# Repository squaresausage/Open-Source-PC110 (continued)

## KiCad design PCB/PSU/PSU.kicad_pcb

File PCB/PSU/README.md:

## Here is the PCB Layout for the PSU board

Layer Stack-up

| Index | Layer name | Description  |
| ----- | ---------- | ------------ |
| 1     | FC         | Top          |
| 2     | IC         | Signal       |
| 3     | IP         | Ground       |
| 4     | BC         | Bottom       |

Here is a render of FC, IC, IP and BC:

Here are 3D models of the PSU board:

PCB statistics report
=====================
- Date: Saturday, March 15, 2025 at 01:16:45 PM
- Project: PSU
- Board name: PSU

Board
-----
- Width: 72.3100 mm
- Height: 44.9600 mm
- Area: 2701.6649 mm²

Pads
----
- Through hole: 20
- SMD: 688
- Connector: 0
- NPTH: 0

Vias
----
- Through vias: 212
- Blind/buried: 0
- Micro vias: 0

Components
----------

|              | Front Side | Back Side | Total |
|--------------|------------|-----------|-------|
|THT:          |          0 |        10 |    10 |
|SMD:          |        171 |        76 |   247 |
|Unspecified:  |          1 |         0 |     1 |
|Total:        |        172 |        86 |   258 |

Drill holes
-----------

| Count | Shape |    X Size |    Y Size | Plated | Via/Pad | Start Layer | Stop Layer |
|-------|-------|-----------|-----------|--------|---------|-------------|------------|
|   203 | Round | 0.3000 mm | 0.3000 mm |    PTH |     Via |          FC |         BC |
|    14 | Round | 0.8000 mm | 0.8000 mm |    PTH |     Pad |          FC |         BC |
|     6 | Round | 1.3000 mm | 1.3000 mm |    PTH |     Pad |          FC |         BC |
|     5 | Round | 0.8000 mm | 0.8000 mm |    PTH |     Via |          FC |         BC |
|     3 | Round | 0.6000 mm | 0.6000 mm |    PTH |     Via |          FC |         BC |
|     1 | Round | 1.0000 mm | 1.0000 mm |    PTH |     Via |          FC |         BC |

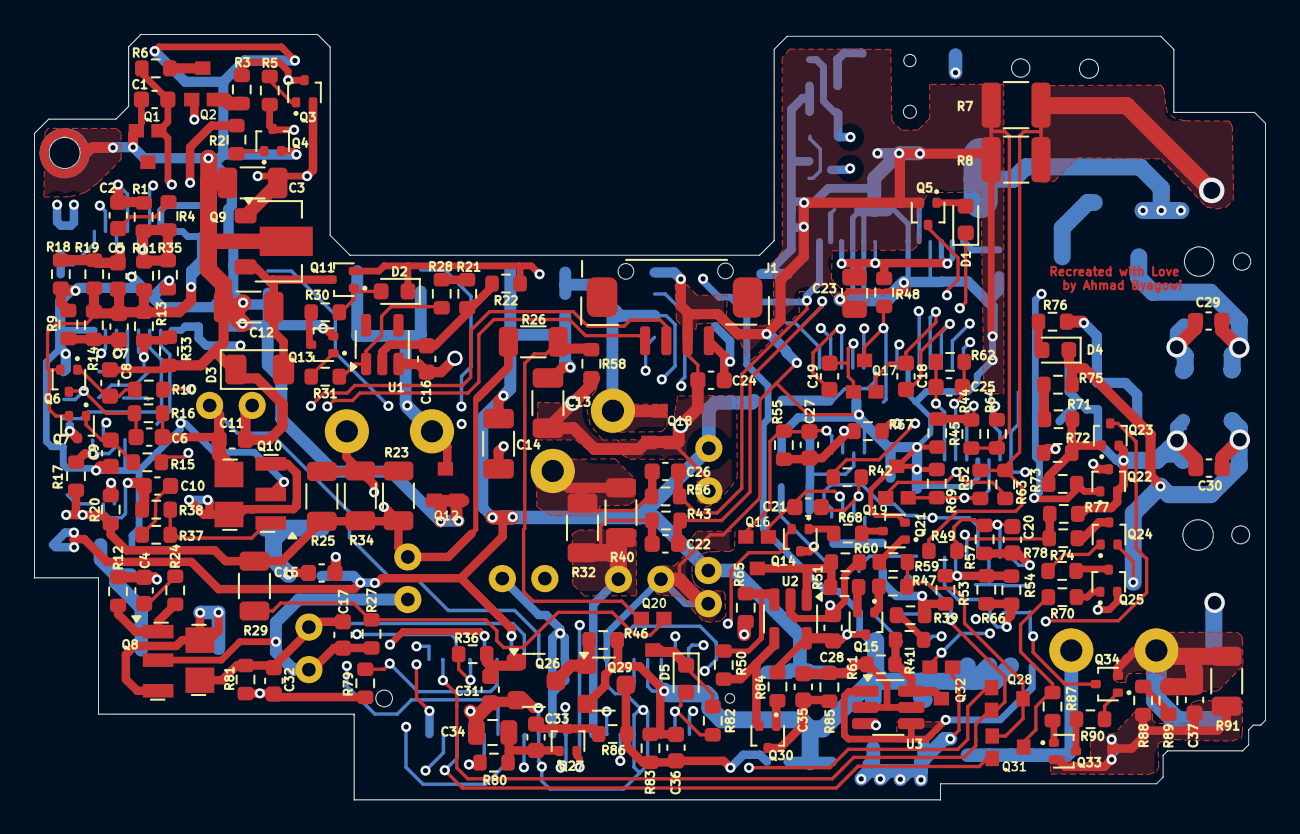
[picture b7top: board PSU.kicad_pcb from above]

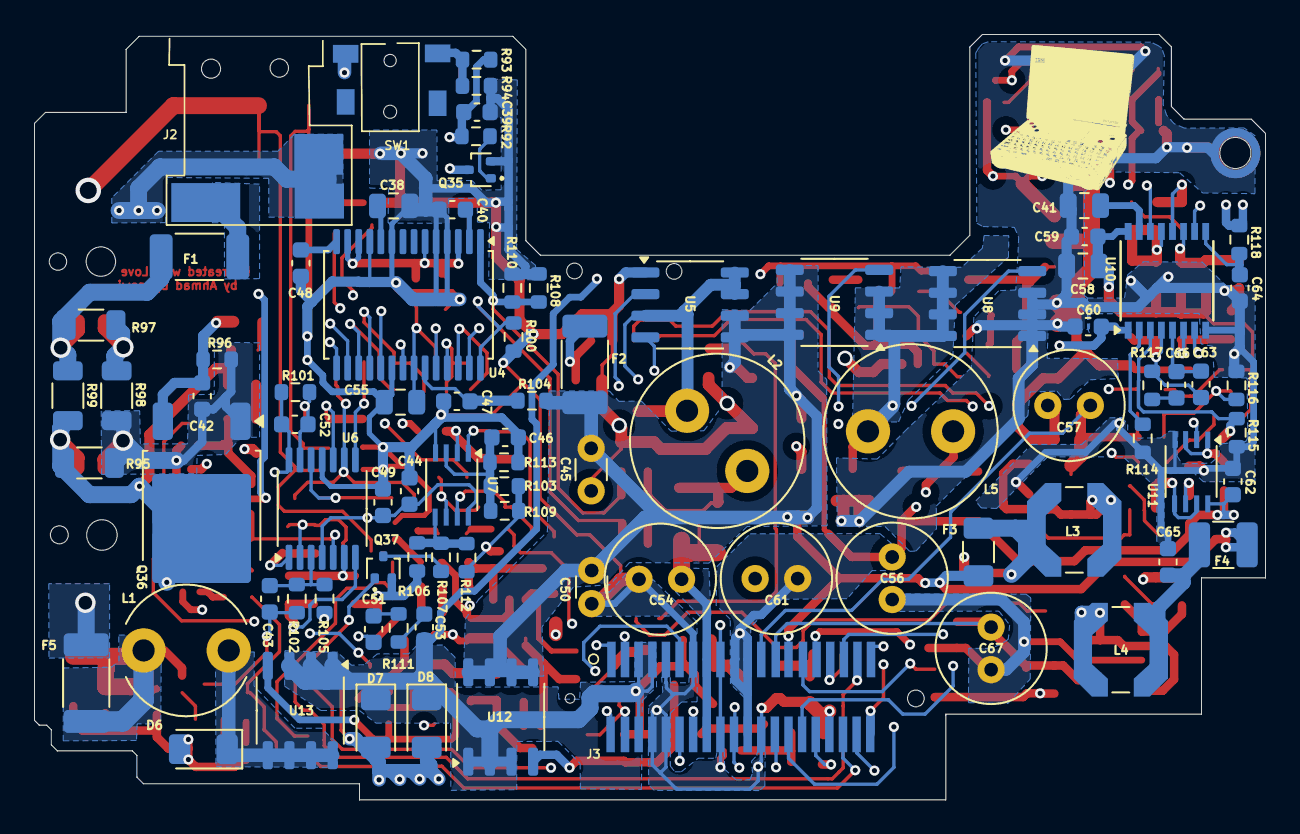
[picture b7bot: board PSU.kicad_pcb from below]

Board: 4 copper layers, 72.3 x 45.0 mm, 258 parts (87 on the bottom side), 155 nets.

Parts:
C1, C5, C7, C16, C24, C28, C36, C46, C47, C59: 150nF; C_0603_1608Metric
C2: 4.7nF; C_0603_1608Metric
C3: 5.2uF; C_1206_3216Metric
C4: 2.5nF; C_0603_1608Metric
C6, C20: 100pF; C_0603_1608Metric
C8, C33: 24nF; C_0603_1608Metric
C9, C17, C22, C26, C29, C30, C32, C39, C40, C48: 10nF; C_0603_1608Metric
C10: 3.6nF; C_0603_1608Metric
C11, C15, C37, C44, C49: 180nF; C_0603_1608Metric
C12: 1.2uF; C_1206_3216Metric
C13, C14: 1.5uF; C_1206_3216Metric
C18, C42, C51, C53, C64: 120nF; C_0603_1608Metric
C19: 18nF; C_0603_1608Metric
C21: 12nF; C_0603_1608Metric
C23, C34, C38, C41, C55, C58: 1.5uF; C_0805_2012Metric
C25, C27, C31, C35, C66: 1.2nF; C_0603_1608Metric
C43: 10pF; C_0603_1608Metric
C45: 33uF 20V; C_Disc_D3.0mm_W1.6mm_P2.50mm
C50: 56uF 25V EC; EC
C52, C60: 1nF; C_0603_1608Metric
C54, C61: 47uF 6.3v; C_Radial_D6.3mm_H11.0mm_P2.50mm
C56: 47uF 6.3V; C_Radial_D6.3mm_H11.0mm_P2.50mm
C57: 15uF 16V; C_Radial_D6.3mm_H11.0mm_P2.50mm
C62, C65: 100nF; C_0603_1608Metric
C63: 5.1nF; C_0603_1608Metric
C67: 18uF 50V; C_Radial_D6.3mm_H11.0mm_P2.50mm
D1: 8-2; D_0603_1608Metric
D2: 5-9; D_0603_1608Metric
D3, D6: DNP; D_1206_3216Metric
D4: 18; D_0603_1608Metric
D5: 3^9; D_0603_1608Metric
D7, D8: s.3 4F; D_1206_3216Metric
F1, F5: 2.5A; Fuse_2010_5025Metric
F2: 830mA; Fuse_2010_5025Metric
F3: 15; Fuse_1206_3216Metric
F4: 10; Fuse_1210_3225Metric
G1: LOGO; logo
J1: Backllight_Connector
J2: PSU_Jack
J3: PSU_Connector_Receptor
L1: 10uH; L_Radial_D7.5mm_P5.00mm_Fastron_07P
L2, L5: 10uH; L_Radial_D10.0mm_P5.00mm_Fastron_07M
L3: 68uH; L_Coilcraft_LPS5030
L4: 470uH; L_Coilcraft_LPS5030
Q1: R4C; 3D
Q2, Q32: K; 3D
Q3, Q6, Q7, Q11, Q14, Q24, Q34: 6LS; SOT-416
Q4, Q13, Q15, Q33, Q37: 8LR; SOT-416
Q5, Q21, Q22, Q23, Q27, Q30, Q35: 8C; SOT-416
Q8: 303 5H; SOT-powerT
Q9: KD 3.E; SOT-89-3
Q10: 103 5G; SOT-powerT
Q12, Q18: Q; 3D
Q16, Q17, Q19: M2P; 3D
Q20, Q28, Q31: W6; 3D
Q25: 8LB; SOT-416
Q26: G16; SOT-23-PC110
Q29: H15; SOT-23-PC110
Q36: 3P4J; TO-252-2
R1, R50, R66, R82, R108: DNP; R_0603_1608Metric
R2, R10, R21, R31, R70, R74, R83, R87, R90: 470k; R_0603_1608Metric
R3, R36, R65, R71, R72, R75, R76, R93: 1k; R_0603_1608Metric
R4, R11, R13, R17, R19, R20, R30, R33, R35, R44, R52, R61, R63, R64, R85, R86, R103, R114, R117: 10k; R_0603_1608Metric
R5, R15, R22, R54, R57, R59, R77, R80, R84, R92, R105: 100k; R_0603_1608Metric
R6, R38: 470; R_0603_1608Metric
R7, R8: 0.1; R_1210_3225Metric
R9, R18, R112, R113: 20k; R_0603_1608Metric
R12: 2.2k; R_0603_1608Metric
R14: 12k; R_0603_1608Metric
R16: 130k; R_0603_1608Metric
R23, R25, R32, R34: 0.1; R_1206_3216Metric
R24: 220; R_0603_1608Metric
R26: 103 (RT1); R_1206_3216Metric
R27, R39, R41, R51, R58, R60, R106: 4.7k; R_0603_1608Metric
R28: 0; R_0603_1608Metric
R29: 103 (RT2); R_1206_3216Metric
R37: 120; R_0603_1608Metric
R40: 0.22; R_1206_3216Metric
R42, R47, R67, R68, R73, R79, R94: 47k; R_0603_1608Metric
R43, R56: 300; R_0603_1608Metric
R45, R62, R69, R81, R101, R109: 200k; R_0603_1608Metric
R46, R55, R88, R89: 1M; R_0603_1608Metric
R48, R104, R118: 100; R_0603_1608Metric
R49, R53, R78, R102: 300k; R_0603_1608Metric
R91, R95, R97: DNP; R_1206_3216Metric
R96: 1.8k; R_0603_1608Metric
R98, R99: 0; R_1206_3216Metric
R100, R110: 7.5k; R_0603_1608Metric
R107: 2k; R_0603_1608Metric
R111: 33; R_0603_1608Metric
R115: 11K; R_0603_1608Metric
R116: 15k; R_0603_1608Metric
SW1: PSU-SW1
U1: D9D; SOT-23-5
U2: TA; SOT-23-5
U3: 6.5 5F; SOT-23-6_Handsoldering
U4: MAX786CAI; TSSOP-28_6.1x9.7mm_P0.65mm
U5: K2337; SOP-8_3.9x4.9mm_P1.27mm
U6: 7064; TSSOP-14_4.4x5mm_P0.65mm
U7: 5W01; SSOP-8-PSU
U8, U9: 2556; SOP-8_3.9x4.9mm_P1.27mm
U10: 9742; SSOP-16_4.4x5.2mm_P0.65mm
U11: 7W14; SSOP-8-PSU
U12, U13: J421; SOP-8_3.9x4.9mm_P1.27mm

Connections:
BATT_POS: R7.2, R8.2, R49.1, R52.2, R63.2
C1_1: C2.1, R4.1
C1_2: C2.2, R1.1, U10.12
C6_1: C4.1, R24.2
C6_2: C4.2, R12.2, U11.2
C8_1: C7.1, R9.2, R14.2, U10.6
C14_2: C12.2, D3.2, Q9.3, Q11.3
C31_1: C33.1, Q27.3, R86.2
C32_1: C33.2, C34.1, Q27.1, R80.1
C33_1: C31.1, Q26.1, R36.1
C35_2: C36.2, Q29.3, R83.2, R86.1, U12.4
C36_1: C35.1, R61.1, R85.2, U3.2, U3.5
C36_2: C35.2, Q30.3, R85.1
D1_2: D1.2, Q5.1
D2_3_PC110: J3.26, Q23.3
D18_2_3_PC110: J1.1, J3.40
D28_1_PC110: C6.2, C11.1, C57.1, J3.12, Q10.4, R16.2
F3_1: C15.1, F3.1, L3.1
F65_ENAVEE_PC110: J3.35, R15.1
GND: C1.1, C3.1, C8.2, C9.1, C11.2, C12.1, C13.2, C14.2, C15.2, C16.2, C17.1, C23.1, C24.1, C28.1, C30.1, C31.2, C34.2, C37.1, C38.2, C39.2, C40.1, C41.1, C42.2, C44.2, C45.1, C46.2, C47.1, C48.2, C49.2, C50.1, C51.1, C54.2, C55.1, C56.1, C57.2, C58.1, C59.2, C60.1, C61.2, C62.1, C64.2, C65.2, C67.1, D3.1, D6.2, J1.3, J3.5, J3.7, J3.9, J3.24, J3.25, J3.29, J3.32, J3.37, Q1.1, Q4.2, Q5.2, Q8.2, Q9.2, Q10.2, Q12.1, Q12.3, Q13.2, Q18.1, Q18.3, Q19.2, Q21.2, Q22.2, Q23.2, Q25.2, Q26.2, Q27.2, Q33.2, Q35.2, Q36.1, Q37.2, R7.1, R8.1, R9.1, R18.2, R27.1, R33.2, R35.2, R39.2, R44.1, R45.1, R53.1, R58.1, R60.2, R64.1, R69.2, R72.1, R77.2, R88.1, R91.1, R94.2, R95.2, R96.2, R98.2, R100.2, R105.2, R106.2, R108.1, R110.1, R113.2, R114.2, R115.2, R116.1, U1.3, U2.2, U3.3, U4.4, U4.5, U4.9, U4.11, U4.20, U5.1, U6.11, U7.4, U8.1, U8.2, U8.3, U10.8, U11.4
J1_4: C24.2, F2.1, J1.4
J5_6_PC110: D1.1, J3.6, Q32.1
J5_33_PC110: C39.1, J3.33, R92.1, R93.2
JRC_IN1+: C43.1, R102.1, R105.1, U6.3
JRC_IN1-: C20.2, R49.2, R57.2, U6.2
JRC_IN2+: R77.1, R78.1, U6.5
JRC_IN2-: R53.2, R54.2, R66.2, U6.6
JRC_IN3+: R44.2, R45.2, U6.10
JRC_IN3-: C25.2, Q19.3, R62.2, R63.1, U6.9
JRC_IN4+: Q19.1, R52.1, R69.1, U6.12
JRC_IN4-: C52.2, R64.2, R101.2, U6.13
JRC_VDD: C44.1, C49.1, Q3.3, R3.1, U6.4, U7.8
L1_2: D6.1, L1.2, U13.5, U13.6, U13.7, U13.8
L2_2: L3.2, Q10.3, Q10.5
M38_P20_PC110: J3.19, Q28.1, Q37.1
M38_P21_PC110: J3.39, Q28.3
M38_P52_PC110: J3.18, R2.1
M38_P53_PC110: J3.38, Q31.1
M38_P60_PC110: C25.1, J3.1, R62.1, U6.8
M38_P61_PC110: C52.1, J3.2, R42.1, R101.1, U6.14
M38_P63_PC110: C20.1, J3.21, R57.1, R67.2, U6.1
M38_P64_PC110: J3.27, R54.1, R66.1, U6.7
M38_VREF_PC110: C1.2, J3.30, Q1.3, Q14.2, R6.1
MAX_BST3: C19.2, Q17.3, U4.25
MAX_BST5: C18.2, Q17.1, U4.18
MAX_CS3: C26.2, R56.2, R108.2, R110.2, U4.1
MAX_CS5: L5.1, R23.2, R25.2, R34.2, U4.15
MAX_DH3: U4.27, U5.4
MAX_DH5: U4.16, U9.4
MAX_DL3: U4.24, U5.2
MAX_DL5: U4.19, U8.4
MAX_FB3: C22.2, R43.2, R100.1, U4.28
MAX_LX3: C19.1, L2.1, Q18.2, U4.26, U5.3, U5.7, U5.8
MAX_LX5: C18.1, L5.2, Q12.2, U4.17, U8.5, U8.6, U8.7, U8.8, U9.1, U9.2, U9.3
MAX_REF: C38.1, U4.10
MAX_SS3: C40.2, U4.2
MAX_SS5: C48.1, U4.14
MAX_VL: C55.2, Q17.2, R48.1, U4.22
MAX_VL+: C47.2, R104.1, U4.23
ON3_ON5_VH_SHDN#: C23.2, R48.2, U4.3, U4.6, U4.12, U4.13
PNET1_PC110: C22.1, C54.1, J3.8, J3.28, R32.1, R40.1, R43.1
PNET4_PC110: C36.1, C53.2, D2.1, D7.1, D8.1, J3.3, J3.4, J3.23, Q11.2, Q29.2, R22.2, R46.2, R83.1, U12.1, U12.2, U12.3, U13.1, U13.2, U13.3
PNET5_PC110: C28.2, C56.2, C61.1, C62.2, J3.10, J3.11, J3.31, Q2.3, Q15.3, R17.2, R20.2, R23.1, R25.1, R26.1, R29.2, R34.1, R84.2, R118.1, U2.5, U4.21, U11.8
PWR_IN_10v5: C30.2, D4.1, D7.2, D8.2, Q24.2, Q32.3, Q36.2, R75.2, R95.1, R99.2
PWR_IN_NEG: C29.1, J2.2, J2.3, R97.2, R98.1
PWR_IN_POS: F1.2, J2.1
PWR_IN_POS_Fuse: C29.2, F1.1, R97.1, R99.1
Q3_1: Q4.1, R2.2
Q3_3: Q4.3, Q5.3, Q22.3, R5.2
Q4_1: Q3.1, R5.1
Q6_2: C5.1, C7.2, C58.2, C59.1, Q6.2, Q7.2, R11.2, R13.1, R14.1, R19.2, U10.16
Q7_1: C8.1, Q6.1, R10.1
Q7_3: C6.1, Q6.3, R16.1, R116.2, U10.14
Q8_1: Q8.1, R12.1, R24.1
Q8_5: L4.1, Q8.3, Q8.5
Q9_1: Q10.1, R37.1, R38.1
Q13_3: Q13.3, R30.1
Q14_2: D5.1, Q20.2, R82.1
Q20_1: C27.2, Q16.1, R55.2, U7.1
Q22_1: Q24.1, R74.1
Q27_3: Q26.3, Q29.1, R46.1
Q29_2: Q31.2, R70.1, R87.2
Q30_2: Q28.2, Q31.3, R47.2, R59.2
Q33_2: C37.2, F5.2, L1.1, Q34.2, R89.2, R91.2
Q33_3: C43.2, Q34.3, R102.2
Q36_3: Q37.3, R107.2
Q43_2_PC110: C17.2, C32.2, C67.2, J3.13, Q8.4, R81.2
Q49_1_PC110: D5.2, J3.22, R82.2
R2_2: Q2.1, R3.2
R6_2: Q2.2, R6.2
R11_1: R20.1, U10.7, U11.6
R17_2: C9.2, Q7.1, R15.2
R19_1: R17.1, U10.10, U11.1, U11.3
R20_1: C5.2, R18.1, R19.1, U10.11
R21_1: Q13.1, R31.1
R21_2: R28.1, R31.2, U1.1
R24_2: C10.1, R38.2, U11.5, U11.7
R26_2: R21.2, R28.2
R31_1: C16.1, R21.1, R22.1, U1.2
R32_1: R1.2, R4.2, R11.1, R35.1, U10.13
R35_2: D2.2, Q11.1, R30.2
R36_1: C63.2, R13.2, R33.1, R117.1, U10.4
R36_2: C10.2, R37.2
R38_1: Q20.3, R27.2, R29.1
R48_2: Q20.1, R26.2, R58.2
R50_1: Q30.2, R50.1, U2.4
R50_2: R50.2, R65.2, U2.3
R51_1: Q16.2, R51.1, R60.1, U2.1
R51_2: Q15.2, R51.2
R54_2: R39.1, R41.2
R56_1: C26.1, L2.2, R32.2, R40.2, R56.1
R59_1: Q21.1, R59.1
R61_1: Q15.1, R47.1
R68_1: Q14.1, R68.1
R68_2: Q21.3, R68.2
R70_2: Q25.3, R74.2
R72_1: D4.2, R76.1
R72_2: C42.1, Q36.3, R76.2, R96.1
R73_2: Q25.1, R70.2
R73_2_PC110: J3.15, R79.2
R76_1: R71.1, R75.1
R77_1: Q23.1, R71.2, R72.2, R73.1
R77_2: Q22.1, Q35.3, R73.2
R78_2: Q24.3, R78.2
R80_1: C32.1, Q7.3, R79.1, R81.1, R115.1, U10.3
R82_1: Q30.1, R84.1
R88_1: Q33.1, R87.1
R89_1: R88.2, R89.1
R91_1: Q33.3, R90.1
R91_2: Q34.1, R90.2
R92_2: Q35.1, R92.2
R104_1: R106.1, R107.1, R112.1, U7.5
R106_1: C51.2, R111.1
R106_2: C53.1, R111.2
R111_2: Q14.3, R103.2, R109.2, R112.2
R111_!: C46.1, R103.1, R109.1, R113.1, U7.3
R115_2: C66.2, R117.2
R284_2_PC110: C13.1, C14.1, C45.2, C50.2, F2.2, F3.2, F4.2, J3.14, R104.2, U5.5, U5.6, U9.5, U9.6, U9.7, U9.8, U12.5, U12.6, U12.7, U12.8
R284_2_PC110_Fuse: C65.1, F4.1, L4.2
R412_1_PC110: J1.2, J3.20
SW1_2: R93.1, R94.1, SW1.2
U3_1: U3.1, U3.4, U13.4
U3_6: Q32.2, R41.1, R61.2, U3.6
U6_2: C27.1, R55.1, R67.1, U7.2
U6_6: C21.1, R42.2, U7.6
U6_7: C21.2, Q16.3, U7.7
U11_1: C60.2, R65.1, U10.1
U11_2: R114.1, U10.2
U11_5: C63.1, C66.1, U10.5
U11_9: C64.1, R118.2, U10.9
U11_15: C41.2, U10.15
U21_131_PC110: J3.34, R10.2
U54_1D_PC110: J3.17, R36.2
U54_1Q_PC110: J3.36, R80.2
U54_VCC_PC110: C3.2, J3.16, Q3.2, Q9.1, SW1.1

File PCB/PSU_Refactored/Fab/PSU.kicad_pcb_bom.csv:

Designator,Quantity,Value,Footprint,Package,MPN,DNP,Mount_Type
"C1, C16, C24, C28, C36, C46, C47, C5, C59, C7",10,150nF,C_0603_1608Metric,,,,smt
C10,1,3.6nF,C_0603_1608Metric,,,,smt
"C11, C15, C37, C44, C49",5,180nF,C_0603_1608Metric,,,,smt
C12,1,1.2uF,C_1206_3216Metric,,,,smt
"C13, C14",2,1.5uF,C_1206_3216Metric,,,,smt
"C17, C22, C26, C29, C30, C32, C39, C40, C48, C9",10,10nF,C_0603_1608Metric,,,,smt
"C18, C42, C51, C53, C64",5,120nF,C_0603_1608Metric,,,,smt
C19,1,18nF,C_0603_1608Metric,,,,smt
C2,1,4.7nF,C_0603_1608Metric,,,,smt
"C20, C6",2,100pF,C_0603_1608Metric,,,,smt
C21,1,12nF,C_0603_1608Metric,,,,smt
"C23, C34, C38, C41, C55, C58",6,1.5uF,C_0805_2012Metric,,,,smt
"C25, C27, C31, C35, C66",5,1.2nF,C_0603_1608Metric,,,,smt
C3,1,5.2uF,C_1206_3216Metric,,,,smt
"C33, C8",2,24nF,C_0603_1608Metric,,,,smt
C4,1,2.5nF,C_0603_1608Metric,,,,smt
C43,1,10pF,C_0603_1608Metric,,,,smt
C45,1,33uF 20V,C_Disc_D3.0mm_W1.6mm_P2.50mm,,,,tht
C50,1,56uF 25V EC,EC,,,,tht
"C52, C60",2,1nF,C_0603_1608Metric,,,,smt
"C54, C61",2,47uF 6.3v,C_Radial_D6.3mm_H11.0mm_P2.50mm,,,,tht
C56,1,47uF 6.3V,C_Radial_D6.3mm_H11.0mm_P2.50mm,,,,tht
C57,1,15uF 16V,C_Radial_D6.3mm_H11.0mm_P2.50mm,,,,tht
"C62, C65",2,100nF,C_0603_1608Metric,,,,smt
C63,1,5.1nF,C_0603_1608Metric,,,,smt
C67,1,18uF 50V,C_Radial_D6.3mm_H11.0mm_P2.50mm,,,,tht
D1,1,8-2,D_0603_1608Metric,,,,smt
D2,1,5-9,D_0603_1608Metric,,,,smt
D3,1,DNP,D_1206_3216Metric,,,Yes,smt
D4,1,18,D_0603_1608Metric,,,,smt
D5,1,3^9,D_0603_1608Metric,,,,smt
D6,1,DNP,D_1206_3216Metric,,,Yes,smt
"D7, D8",2,s.3 4F,D_1206_3216Metric,,,,smt
"F1, F5",2,2.5A,Fuse_2010_5025Metric,,,,smt
F2,1,830mA,Fuse_2010_5025Metric,,,,smt
F3,1,15,Fuse_1206_3216Metric,,,,smt
F4,1,10,Fuse_1210_3225Metric,,,,smt
J1,1,Backllight_Connector,Backllight_Connector,,,,smt
J2,1,PSU_Jack,PSU_Jack,,,,smt
J3,1,PSU_Connector_Receptor,PSU_Connector_Receptor,,,,smt
L1,1,10uH,L_Radial_D7.5mm_P5.00mm_Fastron_07P,,,,tht
"L2, L5",2,10uH,L_Radial_D10.0mm_P5.00mm_Fastron_07M,,,,tht
L3,1,68uH,L_Coilcraft_LPS5030,,,,smt
L4,1,470uH,L_Coilcraft_LPS5030,,,,smt
Q1,1,R4C,3D,,,,smt
Q10,1,103 5G,SOT-powerT,,,,smt
"Q11, Q14, Q24, Q3, Q34, Q6, Q7",7,6LS,SOT-416,,,,smt
"Q12, Q18",2,Q,3D,,,,smt
"Q13, Q15, Q33, Q37, Q4",5,8LR,SOT-416,,,,smt
"Q16, Q17, Q19",3,M2P,3D,,,,smt
"Q2, Q32",2,K,3D,,,,smt
"Q20, Q28, Q31",3,W6,3D,,,,smt
"Q21, Q22, Q23, Q27, Q30, Q35, Q5",7,8C,SOT-416,,,,smt
Q25,1,8LB,SOT-416,,,,smt
Q26,1,G16,SOT-23-PC110,,,,smt
Q29,1,H15,SOT-23-PC110,,,,smt
Q36,1,3P4J,TO-252-2,,,,smt
Q8,1,303 5H,SOT-powerT,,,,smt
Q9,1,KD 3.E,SOT-89-3,,,,smt
R1,1,DNP,R_0603_1608Metric,,,Yes,smt
"R10, R2, R21, R31, R70, R74, R83, R87, R90",9,470k,R_0603_1608Metric,,,,smt
"R100, R110",2,7.5k,R_0603_1608Metric,,,,smt
"R101, R109, R45, R62, R69, R81",6,200k,R_0603_1608Metric,,,,smt
"R102, R49, R53, R78",4,300k,R_0603_1608Metric,,,,smt
"R103, R11, R114, R117, R13, R17, R19, R20, R30, R33, R35, R4, R44, R52, R61, R63, R64, R85, R86",19,10k,R_0603_1608Metric,,,,smt
"R104, R118, R48",3,100,R_0603_1608Metric,,,,smt
"R105, R15, R22, R5, R54, R57, R59, R77, R80, R84, R92",11,100k,R_0603_1608Metric,,,,smt
"R106, R27, R39, R41, R51, R58, R60",7,4.7k,R_0603_1608Metric,,,,smt
R107,1,2k,R_0603_1608Metric,,,,smt
R108,1,DNP,R_0603_1608Metric,,,Yes,smt
R111,1,33,R_0603_1608Metric,,,,smt
"R112, R113, R18, R9",4,20k,R_0603_1608Metric,,,,smt
R115,1,11K,R_0603_1608Metric,,,,smt
R116,1,15k,R_0603_1608Metric,,,,smt
R12,1,2.2k,R_0603_1608Metric,,,,smt
R14,1,12k,R_0603_1608Metric,,,,smt
R16,1,130k,R_0603_1608Metric,,,,smt
"R23, R25, R32, R34",4,0.1,R_1206_3216Metric,,,,smt
R24,1,220,R_0603_1608Metric,,,,smt
R26,1,103 (RT1),R_1206_3216Metric,,,,smt
R28,1,0,R_0603_1608Metric,,,,smt
R29,1,103 (RT2),R_1206_3216Metric,,,,smt
"R3, R36, R65, R71, R72, R75, R76, R93",8,1k,R_0603_1608Metric,,,,smt
R37,1,120,R_0603_1608Metric,,,,smt
"R38, R6",2,470,R_0603_1608Metric,,,,smt
R40,1,0.22,R_1206_3216Metric,,,,smt
"R42, R47, R67, R68, R73, R79, R94",7,47k,R_0603_1608Metric,,,,smt
"R43, R56",2,300,R_0603_1608Metric,,,,smt
"R46, R55, R88, R89",4,1M,R_0603_1608Metric,,,,smt
R50,1,DNP,R_0603_1608Metric,,,Yes,smt
R66,1,DNP,R_0603_1608Metric,,,Yes,smt
"R7, R8",2,0.1,R_1210_3225Metric,,,,smt
R82,1,DNP,R_0603_1608Metric,,,Yes,smt
R91,1,DNP,R_1206_3216Metric,,,Yes,smt
R95,1,DNP,R_1206_3216Metric,,,Yes,smt
R96,1,1.8k,R_0603_1608Metric,,,,smt
R97,1,DNP,R_1206_3216Metric,,,Yes,smt
"R98, R99",2,0,R_1206_3216Metric,,,,smt
SW1,1,PSU-SW1,PSU-SW1,,,,smt
U1,1,D9D,SOT-23-5,,,,smt
U10,1,9742,SSOP-16_4.4x5.2mm_P0.65mm,,,,smt
U11,1,7W14,SSOP-8-PSU,,,,smt
"U12, U13",2,J421,SOP-8_3.9x4.9mm_P1.27mm,,,,smt
U2,1,TA,SOT-23-5,,,,smt
U3,1,6.5 5F,SOT-23-6_Handsoldering,,,,smt
U4,1,MAX786CAI,TSSOP-28_6.1x9.7mm_P0.65mm,,,,smt
U5,1,K2337,SOP-8_3.9x4.9mm_P1.27mm,,,,smt
U6,1,7064,TSSOP-14_4.4x5mm_P0.65mm,,,,smt
U7,1,5W01,SSOP-8-PSU,,,,smt
"U8, U9",2,2556,SOP-8_3.9x4.9mm_P1.27mm,,,,smt

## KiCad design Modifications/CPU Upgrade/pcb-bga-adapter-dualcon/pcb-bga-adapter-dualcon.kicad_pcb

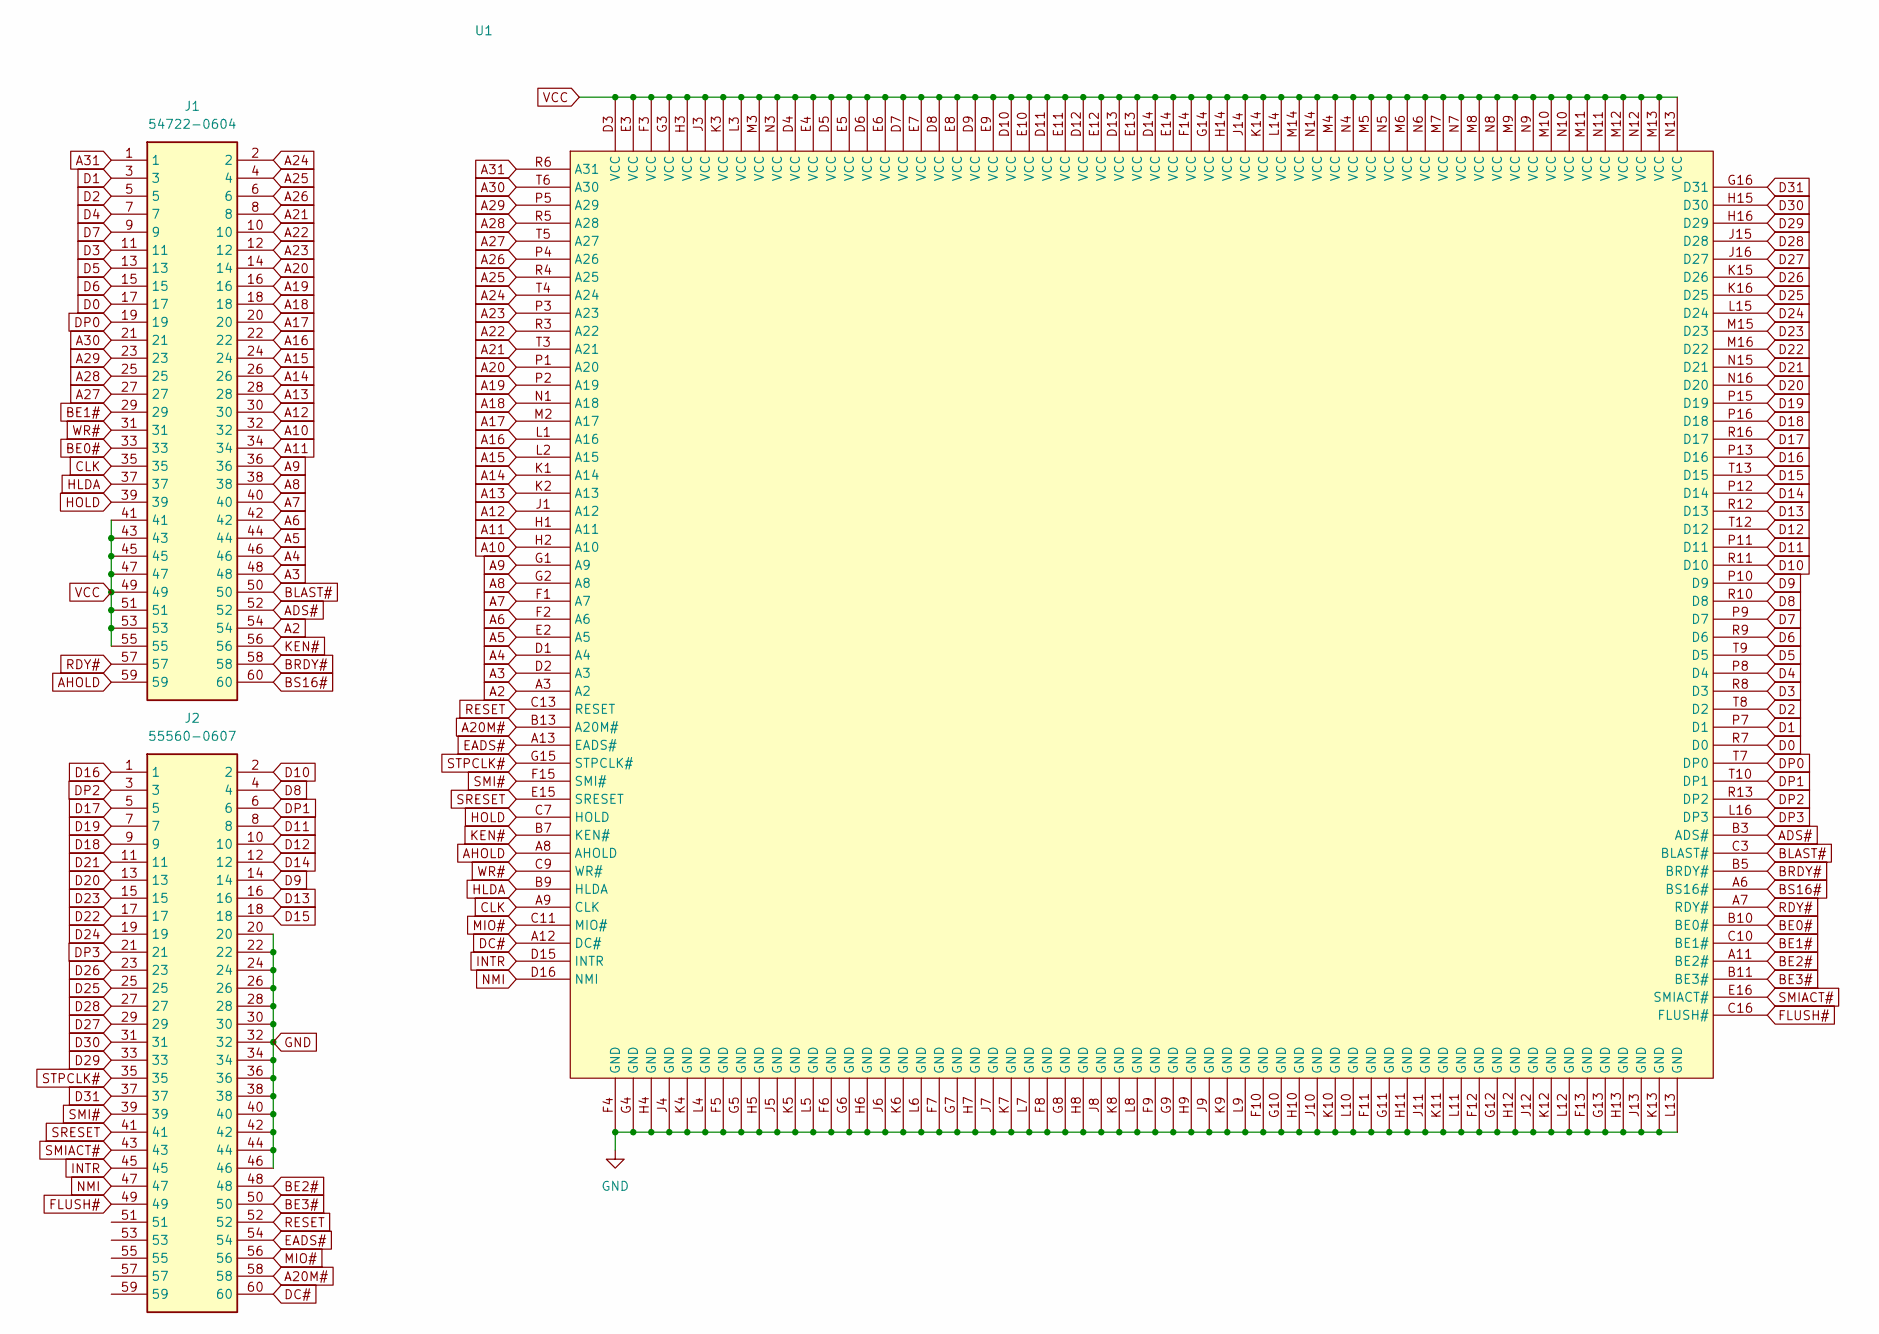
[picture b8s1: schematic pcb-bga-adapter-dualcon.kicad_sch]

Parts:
J1: 54722-0604; 547220604; Mouser Part Number 538-54722-0604
J2: 55560-0607; 555600607; Mouser Part Number 538-55560-0607
U1: BGA-256-MIRRORED

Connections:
A2: J1.54, U1.A3 (A2)
A3: J1.48, U1.D2 (A3)
A4: J1.46, U1.D1 (A4)
A5: J1.44, U1.E2 (A5)
A6: J1.42, U1.F2 (A6)
A7: J1.40, U1.F1 (A7)
A8: J1.38, U1.G2 (A8)
A9: J1.36, U1.G1 (A9)
A10: J1.32, U1.H2 (A10)
A11: J1.34, U1.H1 (A11)
A12: J1.30, U1.J1 (A12)
A13: J1.28, U1.K2 (A13)
A14: J1.26, U1.K1 (A14)
A15: J1.24, U1.L2 (A15)
A16: J1.22, U1.L1 (A16)
A17: J1.20, U1.M2 (A17)
A18: J1.18, U1.N1 (A18)
A19: J1.16, U1.P2 (A19)
A20: J1.14, U1.P1 (A20)
A20M#: J2.58, U1.B13 (A20M#)
A21: J1.8, U1.T3 (A21)
A22: J1.10, U1.R3 (A22)
A23: J1.12, U1.P3 (A23)
A24: J1.2, U1.T4 (A24)
A25: J1.4, U1.R4 (A25)
A26: J1.6, U1.P4 (A26)
A27: J1.27, U1.T5 (A27)
A28: J1.25, U1.R5 (A28)
A29: J1.23, U1.P5 (A29)
A30: J1.21, U1.T6 (A30)
A31: J1.1, U1.R6 (A31)
ADS#: J1.52, U1.B3 (ADS#)
AHOLD: J1.59, U1.A8 (AHOLD)
BE0#: J1.33, U1.B10 (BE0#)
BE1#: J1.29, U1.C10 (BE1#)
BE2#: J2.48, U1.A11 (BE2#)
BE3#: J2.50, U1.B11 (BE3#)
BLAST#: J1.50, U1.C3 (BLAST#)
BRDY#: J1.58, U1.B5 (BRDY#)
BS16#: J1.60, U1.A6 (BS16#)
CLK: J1.35, U1.A9 (CLK)
D0: J1.17, U1.R7 (D0)
D1: J1.3, U1.P7 (D1)
D2: J1.5, U1.T8 (D2)
D3: J1.11, U1.R8 (D3)
D4: J1.7, U1.P8 (D4)
D5: J1.13, U1.T9 (D5)
D6: J1.15, U1.R9 (D6)
D7: J1.9, U1.P9 (D7)
D8: J2.4, U1.R10 (D8)
D9: J2.14, U1.P10 (D9)
D10: J2.2, U1.R11 (D10)
D11: J2.8, U1.P11 (D11)
D12: J2.10, U1.T12 (D12)
D13: J2.16, U1.R12 (D13)
D14: J2.12, U1.P12 (D14)
D15: J2.18, U1.T13 (D15)
D16: J2.1, U1.P13 (D16)
D17: J2.5, U1.R16 (D17)
D18: J2.9, U1.P16 (D18)
D19: J2.7, U1.P15 (D19)
D20: J2.13, U1.N16 (D20)
D21: J2.11, U1.N15 (D21)
D22: J2.17, U1.M16 (D22)
D23: J2.15, U1.M15 (D23)
D24: J2.19, U1.L15 (D24)
D25: J2.25, U1.K16 (D25)
D26: J2.23, U1.K15 (D26)
D27: J2.29, U1.J16 (D27)
D28: J2.27, U1.J15 (D28)
D29: J2.33, U1.H16 (D29)
D30: J2.31, U1.H15 (D30)
D31: J2.37, U1.G16 (D31)
DC#: J2.60, U1.A12 (DC#)
DP0: J1.19, U1.T7 (DP0)
DP1: J2.6, U1.T10 (DP1)
DP2: J2.3, U1.R13 (DP2)
DP3: J2.21, U1.L16 (DP3)
EADS#: J2.54, U1.A13 (EADS#)
FLUSH#: J2.49, U1.C16 (FLUSH#)
GND: J2.20, J2.22, J2.24, J2.26, J2.28, J2.30, J2.32, J2.34, J2.36, J2.38, J2.40, J2.42, J2.44, J2.46, U1.F4 (GND), U1.F5 (GND), U1.F6 (GND), U1.F7 (GND), U1.F8 (GND), U1.F9 (GND), U1.F10 (GND), U1.F11 (GND), U1.F12 (GND), U1.F13 (GND), U1.G4 (GND), U1.G5 (GND), U1.G6 (GND), U1.G7 (GND), U1.G8 (GND), U1.G9 (GND), U1.G10 (GND), U1.G11 (GND), U1.G12 (GND), U1.G13 (GND), U1.H4 (GND), U1.H5 (GND), U1.H6 (GND), U1.H7 (GND), U1.H8 (GND), U1.H9 (GND), U1.H10 (GND), U1.H11 (GND), U1.H12 (GND), U1.H13 (GND), U1.J4 (GND), U1.J5 (GND), U1.J6 (GND), U1.J7 (GND), U1.J8 (GND), U1.J9 (GND), U1.J10 (GND), U1.J11 (GND), U1.J12 (GND), U1.J13 (GND), U1.K4 (GND), U1.K5 (GND), U1.K6 (GND), U1.K7 (GND), U1.K8 (GND), U1.K9 (GND), U1.K10 (GND), U1.K11 (GND), U1.K12 (GND), U1.K13 (GND), U1.L4 (GND), U1.L5 (GND), U1.L6 (GND), U1.L7 (GND), U1.L8 (GND), U1.L9 (GND), U1.L10 (GND), U1.L11 (GND), U1.L12 (GND), U1.L13 (GND)
HLDA: J1.37, U1.B9 (HLDA)
HOLD: J1.39, U1.C7 (HOLD)
INTR: J2.45, U1.D15 (INTR)
KEN#: J1.56, U1.B7 (KEN#)
MIO#: J2.56, U1.C11 (MIO#)
NMI: J2.47, U1.D16 (NMI)
RDY#: J1.57, U1.A7 (RDY#)
RESET: J2.52, U1.C13 (RESET)
SMI#: J2.39, U1.F15 (SMI#)
SMIACT#: J2.43, U1.E16 (SMIACT#)
SRESET: J2.41, U1.E15 (SRESET)
STPCLK#: J2.35, U1.G15 (STPCLK#)
VCC: J1.41, J1.43, J1.45, J1.47, J1.49, J1.51, J1.53, J1.55, U1.D3 (VCC), U1.D4 (VCC), U1.D5 (VCC), U1.D6 (VCC), U1.D7 (VCC), U1.D8 (VCC), U1.D9 (VCC), U1.D10 (VCC), U1.D11 (VCC), U1.D12 (VCC), U1.D13 (VCC), U1.D14 (VCC), U1.E3 (VCC), U1.E4 (VCC), U1.E5 (VCC), U1.E6 (VCC), U1.E7 (VCC), U1.E8 (VCC), U1.E9 (VCC), U1.E10 (VCC), U1.E11 (VCC), U1.E12 (VCC), U1.E13 (VCC), U1.E14 (VCC), U1.F3 (VCC), U1.F14 (VCC), U1.G3 (VCC), U1.G14 (VCC), U1.H3 (VCC), U1.H14 (VCC), U1.J3 (VCC), U1.J14 (VCC), U1.K3 (VCC), U1.K14 (VCC), U1.L3 (VCC), U1.L14 (VCC), U1.M3 (VCC), U1.M4 (VCC), U1.M5 (VCC), U1.M6 (VCC), U1.M7 (VCC), U1.M8 (VCC), U1.M9 (VCC), U1.M10 (VCC), U1.M11 (VCC), U1.M12 (VCC), U1.M13 (VCC), U1.M14 (VCC), U1.N3 (VCC), U1.N4 (VCC), U1.N5 (VCC), U1.N6 (VCC), U1.N7 (VCC), U1.N8 (VCC), U1.N9 (VCC), U1.N10 (VCC), U1.N11 (VCC), U1.N12 (VCC), U1.N13 (VCC), U1.N14 (VCC)
WR#: J1.31, U1.C9 (WR#)

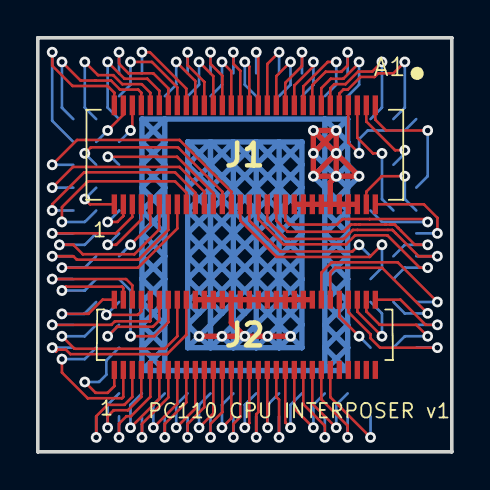
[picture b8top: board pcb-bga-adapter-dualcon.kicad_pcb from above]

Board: 2 copper layers, 23.0 x 23.0 mm, 3 parts (1 on the bottom side), 95 nets.

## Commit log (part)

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2025-04-06 Create M5M27C256AP.pdf
    Datasheet for PROM mode used in M38
2025-06-19 Add part numbers to some SMT parts
2025-06-20 add RAS4
    RAS4 is used to add up to the internal RAM (to make it 8MB)
2025-06-26 fix local and global labels
2025-07-01 Create LICENSE
2025-07-01 Update LICENSE
2025-07-15 A few quick docs cleanups for a broken Hackaday link.
2025-08-21 fixed connection with 3V3 buck output and PNET1
2025-08-21 partially understood U6 code
2025-08-21 Added current state of U6 Disassembly, readme update, better U6 Datasheet
2025-08-21 more readme updates for Ghidra U6 work
2025-08-22 confirmed U6 Crystal freq
2025-08-23 more functions mildly understood...
2025-08-25 Very close to all functions and arrays detected. Only a few instruction issues to debug left
2025-08-30 fixed accidental short of ASIC/U6 line to PNET2 ##In schematic only##
2025-09-15 Made a little PCB that hopefully will reliably read an M38224 with a ROM programmer
2025-09-30 pushing latest disassembly work before encorporating possible bit flips from personal chip read
2025-09-30 Added most patches from personal rom dump. Ghida is faulting when trying to patch arrays though...
2025-10-01 mistyped a patch (wrong ADC version)
2025-10-13 Added files via upload that were accidentally deleted
    Try as I might, my merge cludge broke :( fixing manually. These are the exact files from before the merge.
2025-10-29 updates to disassembly
2025-10-29 Personal notes for PSU understanding
2025-11-04 initial refactored PSU schematic. same number of components but otherwise needs confirmation
2026-02-23 latest work and html output for ease
